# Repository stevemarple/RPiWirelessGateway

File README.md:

# RPiWirelessGateway

A wireless gateway for the Raspberry Pi.

## Preliminary

Preliminary, untested design.

## License

The hardware design released under the Creative Commons Attribution-ShareAlike 
3.0 Unported (CC BY-SA 3.0) license, see 
http://creativecommons.org/licenses/by-sa/3.0/

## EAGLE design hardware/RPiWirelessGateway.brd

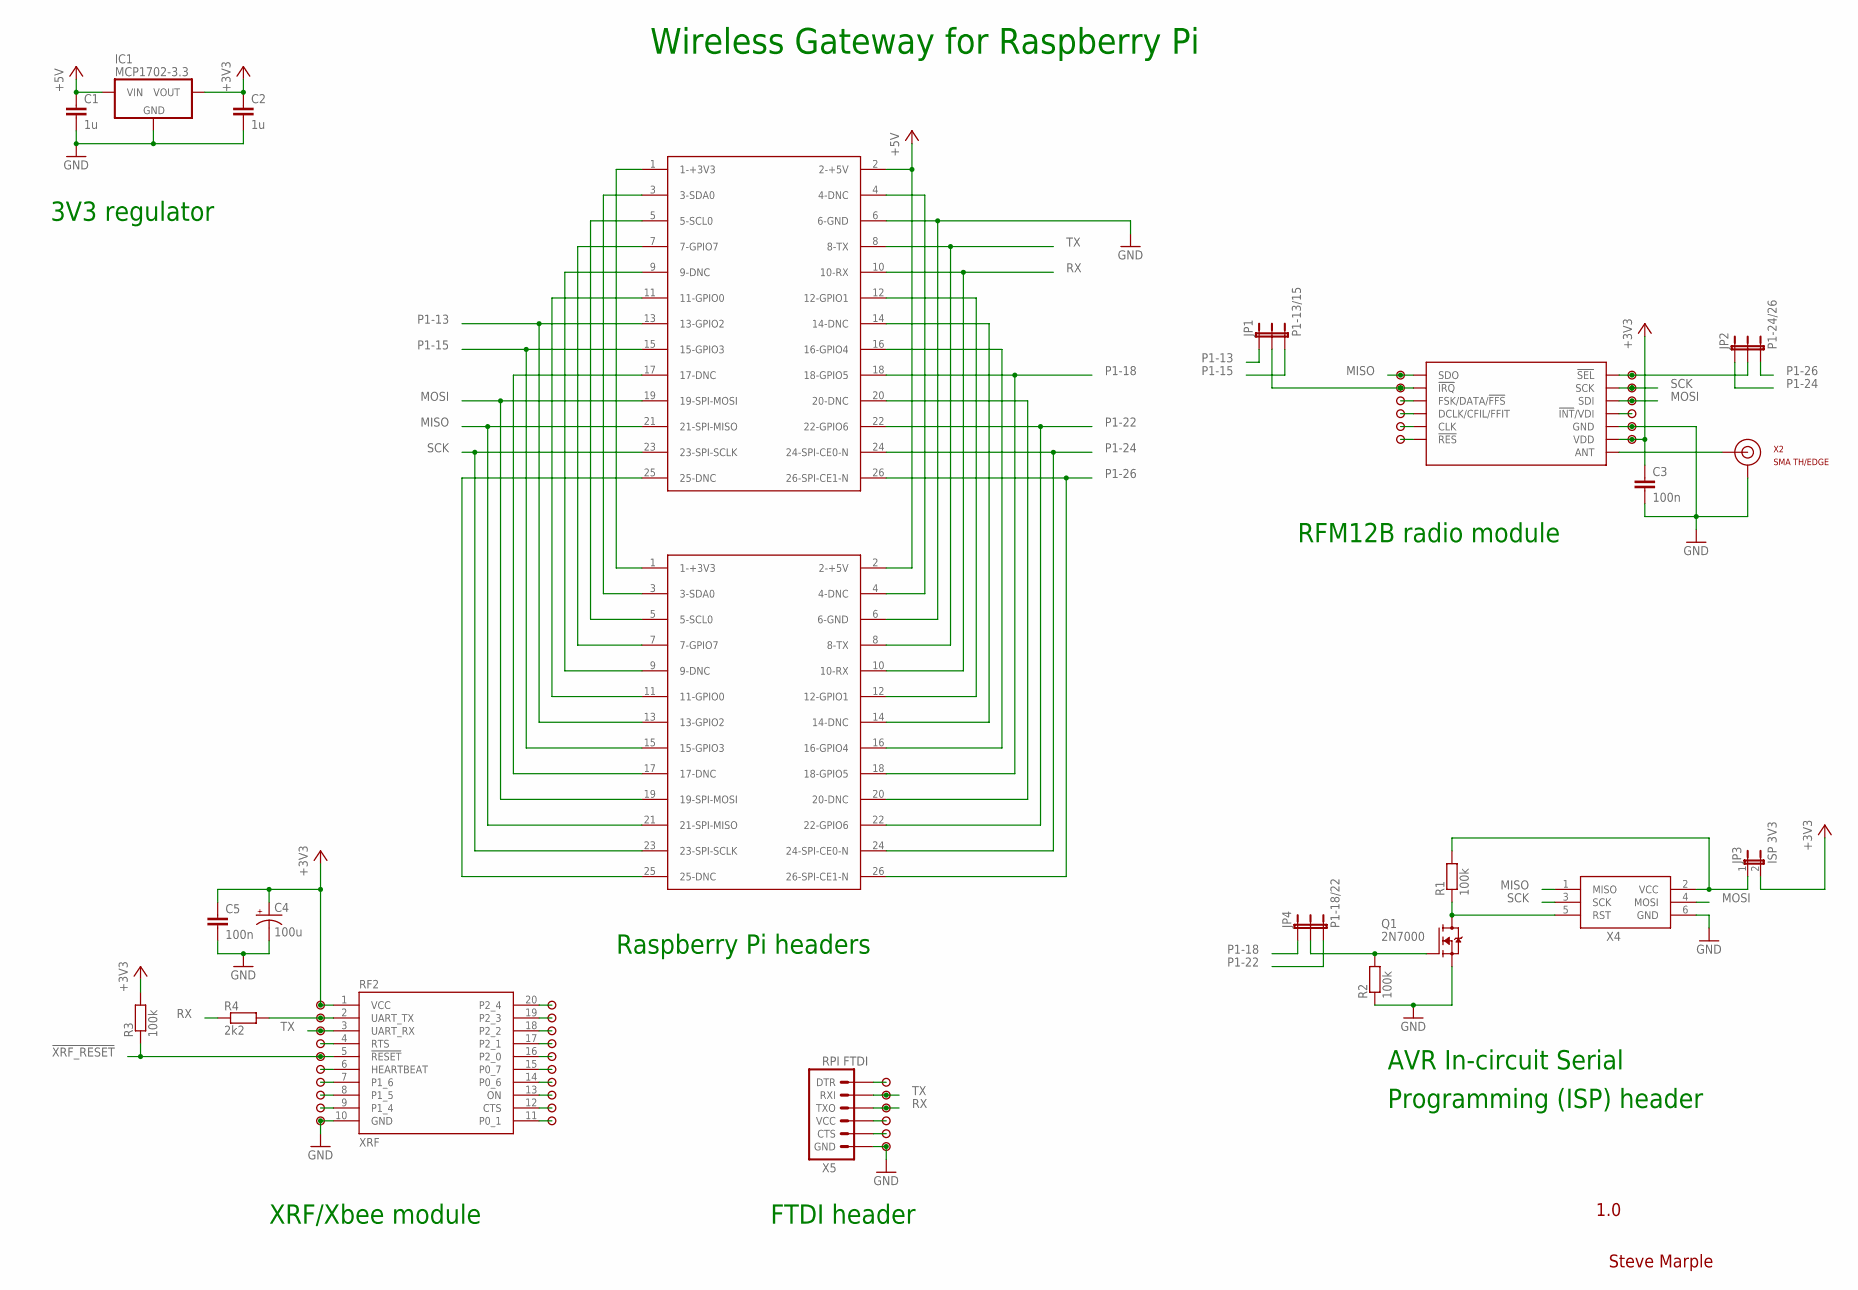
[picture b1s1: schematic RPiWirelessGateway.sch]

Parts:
C1, C2: 1u; CAP-PTH-5MM
C3, C5: 100n; CAP-PTH-SMALL
C4: 100u; CPOL-RADIAL-10UF-25V
IC1: MCP1702-3.3; TO-92
JP1: P1-13/15; 1X03
JP2: P1-24/26; 1X03
JP3: ISP 3V3; 1X02
JP4: P1-18/22; 1X03
PAD_RFM12B_!INT!/VDI, PAD_RFM12B_!INT!/VDI1, PAD_RFM12B_!INT!/VDI2, PAD_RFM12B_!IRQ, PAD_RFM12B_!RESET, PAD_RFM12B_!SEL, PAD_RFM12B_CLK, PAD_RFM12B_DCLK/CFIL/!FFS, PAD_RFM12B_FSK/DATA/!FFS, PAD_RFM12B_SCK, PAD_RFM12B_SDI, PAD_RFM12B_SDO: PAD
Q1: 2N7000; TO-92
R1, R2, R3: 100k; RES-AXIAL-0.4
R4: 2k2; RES-AXIAL-0.4
RF1: RFM12B
RF2: XRF; XBEE
U$1, U$2, U$3, U$4, U$5, U$6, U$7, U$8, U$9, U$10, U$11, U$12, U$13, U$14, U$15, U$16, U$17, U$18, U$19, U$20, U$21, U$22, U$23, U$24, U$25, U$26: PAD
X1: P1A; RASPBERRY-PI-HEADER
X2: SMA TH/EDGE; SMA-THD-EDGE
X3: P1B; RASPBERRY-PI-HEADER
X4: AVR ISP; CONN-HARTING-ML6
X5: RPI FTDI; 1X06-KIT

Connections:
!XRF_RESET: R3.P$1 (1), RF2.5 (!RESET), U$9.1
+3V3: C2.1, C3.1, C4.1 (+), C5.1, IC1.3 (VOUT), JP3.2, PAD_RFM12B_!INT!/VDI2.1, R3.P$2 (2), RF1.VDD, RF2.1 (VCC), U$1.1
+5V: C1.1, IC1.2 (VIN), X1.2 (2-+5V), X3.2 (2-+5V)
GND: C1.2, C2.2, C3.2, C4.2 (-), C5.2, IC1.1 (GND), PAD_RFM12B_!INT!/VDI1.1, Q1.1 (S), R2.P$1 (1), RF1.GND@0 (GND), RF1.GND@1 (GND), RF2.10 (GND), U$22.1, U$26.1, X1.6 (6-GND), X2.GND@0 (GND), X2.GND@1 (GND), X2.GND@2 (GND), X2.GND@3 (GND), X2.GND@EDGE0 (GND), X2.GND@EDGE1 (GND), X2.GND@EDGE2 (GND), X2.GND@EDGE3 (GND), X3.6 (6-GND), X4.6 (GND), X5.6 (GND)
MISO: PAD_RFM12B_SDO.1, RF1.SDO, X1.21 (21-SPI-MISO), X3.21 (21-SPI-MISO), X4.1 (MISO)
MOSI: PAD_RFM12B_SDI.1, RF1.SDI, X1.19 (19-SPI-MOSI), X3.19 (19-SPI-MOSI), X4.4 (MOSI)
unnamed: RF1.ANT, X2.SIG (SIGNAL), X2.SIG@EDGE (SIGNAL)
unnamed: JP2.2, PAD_RFM12B_!SEL.1, RF1.!SEL
unnamed: RF2.4 (RTS), U$7.1
unnamed: JP3.1, R1.P$2 (2), X4.2 (VCC)
unnamed: RF2.6 (HEARTBEAT), U$11.1
unnamed: RF2.7 (P1_6), U$13.1
unnamed: RF2.8 (P1_5), U$16.1
unnamed: RF2.9 (P1_4), U$19.1
unnamed: RF2.11 (P0_1), U$23.1
unnamed: RF2.12 (CTS), U$20.1
unnamed: RF2.13 (ON), U$17.1
unnamed: RF2.14 (P0_6), U$14.1
unnamed: RF2.15 (P0_7), U$12.1
unnamed: RF2.16 (P2_0), U$10.1
unnamed: RF2.17 (P2_1), U$8.1
unnamed: RF2.18 (P2_2), U$6.1
unnamed: RF2.19 (P2_3), U$4.1
unnamed: RF2.20 (P2_4), U$2.1
unnamed: PAD_RFM12B_!INT!/VDI.1, RF1.!INT!/VDI
unnamed: PAD_RFM12B_FSK/DATA/!FFS.1, RF1.FSK/DATA/!FFS
unnamed: PAD_RFM12B_DCLK/CFIL/!FFS.1, RF1.DCLK/CFIL/FFIT
unnamed: PAD_RFM12B_CLK.1, RF1.CLK
unnamed: PAD_RFM12B_!RESET.1, RF1.!RES
unnamed: Q1.3 (D), R1.P$1 (1), X4.5 (RST)
unnamed: X1.3 (3-SDA0), X3.3 (3-SDA0)
unnamed: X1.5 (5-SCL0), X3.5 (5-SCL0)
unnamed: X1.7 (7-GPIO7), X3.7 (7-GPIO7)
unnamed: X1.9 (9-DNC), X3.9 (9-DNC)
unnamed: X1.11 (11-GPIO0), X3.11 (11-GPIO0)
unnamed: U$25.1, X5.5 (CTS)
unnamed: U$24.1, X5.4 (VCC)
unnamed: X1.17 (17-DNC), X3.17 (17-DNC)
unnamed: X1.4 (4-DNC), X3.4 (4-DNC)
unnamed: X1.25 (25-DNC), X3.25 (25-DNC)
unnamed: X1.12 (12-GPIO1), X3.12 (12-GPIO1)
unnamed: X1.14 (14-DNC), X3.14 (14-DNC)
unnamed: X1.16 (16-GPIO4), X3.16 (16-GPIO4)
unnamed: JP4.2, Q1.2 (G), R2.P$2 (2)
unnamed: X1.20 (20-DNC), X3.20 (20-DNC)
unnamed: U$15.1, X5.1 (DTR)
unnamed: X1.1 (1-+3V3), X3.1 (1-+3V3)
unnamed: R4.P$2 (2), RF2.2 (UART_TX), U$3.1
P1-13: JP1.1, X1.13 (13-GPIO2), X3.13 (13-GPIO2)
P1-13/15: JP1.2, PAD_RFM12B_!IRQ.1, RF1.!IRQ
P1-15: JP1.3, X1.15 (15-GPIO3), X3.15 (15-GPIO3)
P1-18: JP4.1, X1.18 (18-GPIO5), X3.18 (18-GPIO5)
P1-22: JP4.3, X1.22 (22-GPIO6), X3.22 (22-GPIO6)
P1-24: JP2.1, X1.24 (24-SPI-CE0-N), X3.24 (24-SPI-CE0-N)
P1-26: JP2.3, X1.26 (26-SPI-CE1-N), X3.26 (26-SPI-CE1-N)
RX: R4.P$1 (1), U$21.1, X1.10 (10-RX), X3.10 (10-RX), X5.3 (TXO)
SCK: PAD_RFM12B_SCK.1, RF1.SCK, X1.23 (23-SPI-SCLK), X3.23 (23-SPI-SCLK), X4.3 (SCK)
TX: RF2.3 (UART_RX), U$5.1, U$18.1, X1.8 (8-TX), X3.8 (8-TX), X5.2 (RXI)

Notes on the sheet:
1.0
Steve Marple
Raspberry Pi headers
RFM12B radio module
XRF/Xbee module
AVR In-circuit Serial
Programming (ISP) header
FTDI header
3V3 regulator
Wireless Gateway for Raspberry Pi

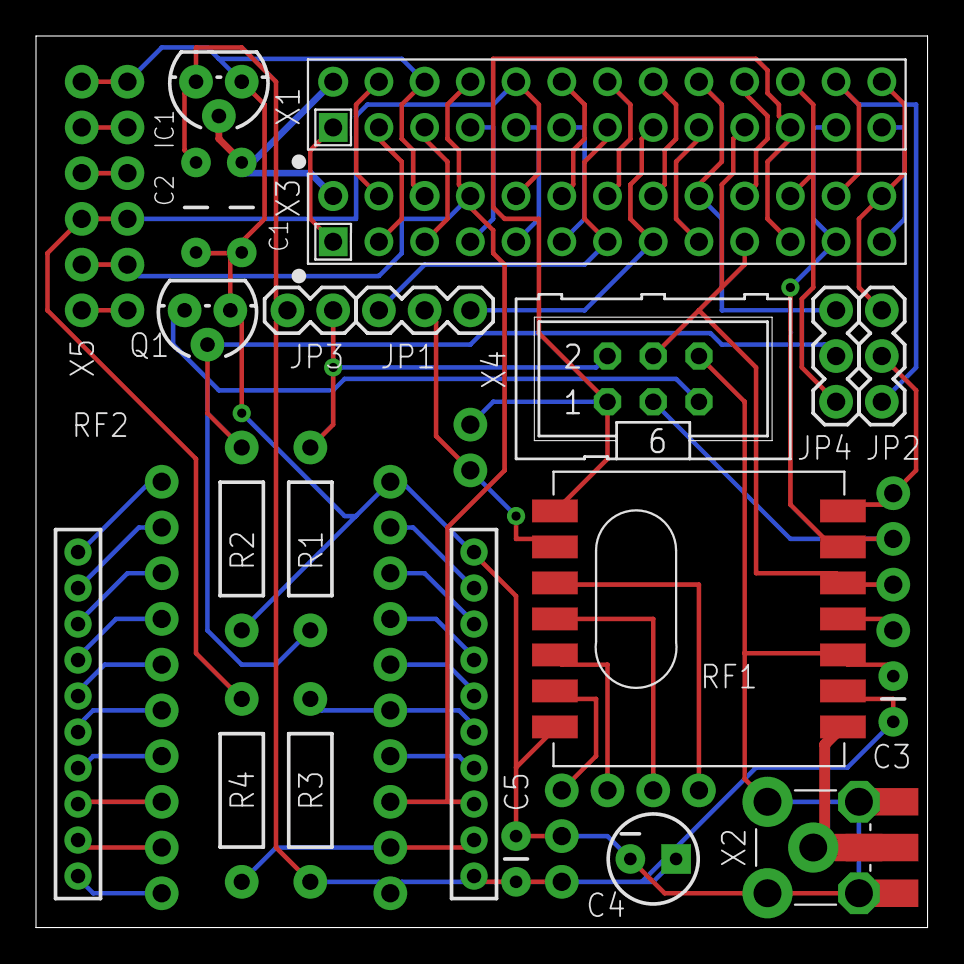
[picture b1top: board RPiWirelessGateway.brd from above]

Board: 2 copper layers, 49.5 x 49.5 mm, 60 parts (0 on the bottom side), 58 nets.

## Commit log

2012-06-30 Adding preliminary hardware design files.
2012-07-01 Adding resistor to XBee TX line to protect if FTDI also fitted simultaneously.
2012-07-01 Updateing readme.
2012-07-08 Adding FET for open-drain control of AVR /RESET
2012-07-09 Added optional pull-up for /FFS. Move breakout pads for XRF/XBee to allow Sparkfun XBee breakout board to be fitted.
2012-07-10 Removed pullup for /FFS (internal pullup present). New RFM12B footprint.

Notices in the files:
hardware/RPiWirelessGateway.brd:
License: CC BY-SA 3.0
parts and their libraries:
SparkFun: Licensing: CC v3.0 Share-Alike You are welcome to use this library for commercial purposes.
